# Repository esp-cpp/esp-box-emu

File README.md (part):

# esp-box-emu

<table style="padding:10px">
    <tr>
        <td></td>
        <td></td>
    </tr>
</table>

> A pocket-sized, Game Boy-style retro **emulation handheld** built around the
> ESP32-S3-BOX. Drop in a micro-SD card of ROMs and play NES, Game Boy / Color,
> Sega, MSX, and Genesis games — plus a full-speed port of **Doom** — on hardware
> you can 3D print and build yourself.

https://github.com/user-attachments/assets/2d3da6ea-2e80-42c3-bbd6-5a2c59601201

<!-- markdown-toc start - Don't edit this section. Run M-x markdown-toc-refresh-toc -->
**Table of Contents**

- [esp-box-emu](#esp-box-emu)
  - [Overview](#overview)
  - [Emulators](#emulators)
  - [Gallery](#gallery)
  - [Quick Start — Play It](#quick-start--play-it)
  - [Web Console](#web-console)
  - [Build the Hardware](#build-the-hardware)
  - [Build the Firmware](#build-the-firmware)
  - [ROMs and SD Card Setup](#roms-and-sd-card-setup)
    - [Boxart images](#boxart-images)
    - [metadata.csv format](#metadatacsv-format)
  - [Features and Roadmap](#features-and-roadmap)
  - [References and Inspiration](#references-and-inspiration)
  - [License](#license)

<!-- markdown-toc end -->

## Overview

The ESP-BOX-EMU turns an [ESP32-S3-BOX or
ESP32-S3-BOX-3](https://github.com/espressif/esp-box) into a handheld retro game
console. A custom add-on board and 3D-printed shell wrap the BOX in a Game Boy
Color form factor — real d-pad and buttons, battery, haptics, and a micro-SD
slot — and the firmware runs a stack of emulators behind a polished LVGL
interface with boxart, save states, and settings.

**Highlights**

- 🎮 **Six systems + Doom** — NES, Game Boy / Color, Sega Master System / Game
  Gear, Sega Genesis, and MSX 1/2 emulators, plus a full-speed **Doom** port —
  all with sound.
- 🧬 **Full-speed Genesis** — a custom **dual-core** port of gwenesis splits the
  emulation across both of the ESP32-S3's cores (CPU + video on one, the sound
  unit on the other) for full-speed Sega Genesis / Mega Drive *with* audio.
- ⚡ **No reboots** — every core and game loads on demand right from the menu, so
  you can jump between titles and even different systems without ever restarting
  the device.
- 🕹️ **Real controls** — d-pad, A/B/X/Y, Start/Select and volume buttons in a
  familiar Game Boy Color layout; the emulator is auto-selected from the ROM
  file extension.
- 💾 **Load from SD** — keep ROMs, boxart, and save states on a micro-SD card,
  and mount the card over USB-C as a mass-storage drive (TinyUSB MSC).
- 💤 **Save anywhere** — up to 5 save slots per game, each with an
  auto-generated screenshot shown in the load menu.
- 🔋 **Portable** — 1000 mAh LiPo battery with USB-C charging.
- 📳 **Haptics** — LRA haptic feedback (DRV2605), including in-game effects in
  Doom (weapon fire, taking damage, pickups, and more).
- 🖼️ **Polished UI** — LVGL menus for ROM select (with boxart) and settings
  (sound, brightness, display scaling, haptics), designed in Squareline Studio.
- 🌐 **Web console** — plug into a computer and Chrome or Edge offers a control
  panel: watch and play the screen, manage games and boxart, browse the SD
  card, change settings, and update the firmware, with nothing to install.
- 🛠️ **Fully open hardware** — 3D-printable GBC-style case and an open PCB
  (Fusion/Eagle **and** [atopile](https://atopile.io) + [KiCad](https://kicad.org)),
  all included in this repo.

## Emulators

The right emulator is chosen automatically from each ROM's file extension, and
games load on demand **straight from the menu — no reboot required**. Pick a
title, play, then drop back to the menu and launch a different game (or a
completely different system) without ever restarting the device. Every core runs
with audio, and several offer an **Unlocked mode** (toggle with the **X** button)
that removes the frame-rate cap for maximum speed.

| System | Core | Unlocked mode | Notes |
| --- | --- | :---: | --- |
| NES | [nofrendo](https://github.com/espressif/esp32-nesemu) | ✅ | D-Pad / A / B / Start / Select |
| Game Boy / Color | [gnuboy](https://github.com/rofl0r/gnuboy) | ✅ | D-Pad / A / B / Start / Select |
| Sega Master System / Game Gear | [smsplus](https://github.com/ekeeke/smsplus-gx) | ✅ | D-Pad / A / B / Start / Select |
| Sega Genesis / Mega Drive | [gwenesis](https://github.com/bzhxx/gwenesis) | — | Full speed with sound; 6-button pad (A→B, B→A, C→Y) |
| MSX 1 / 2 | [fmsx](https://fms.komkon.org/fMSX/) | — | D-Pad / A / B / Start / Select |
| Doom | [prboom](https://prboom.sourceforge.net/) | — | Full speed with audio **and haptic feedback** |
| Dark Forces | [The Force Engine](https://theforceengine.github.io/) (via [BSzili's Amiga port](https://github.com/BSzili/TheForceEngine/tree/amiga)) | — | Software renderer, iMuse sound effects and OPL3 music; see [Dark Forces setup](#dark-forces-setup) |
| PICO-8 | [femto8](https://github.com/benbaker76/femto8) | — | `.p8` and `.p8.png` carts; D-Pad, A/Y = O, B/X = X, START = PICO-8 pause menu; save states; cartdata saves to `pico8/cdata/`; see [PICO-8 setup](#pico-8-setup) |

Every core is a submodule ([esp-cpp/nofrendo](https://github.com/esp-cpp/nofrendo),
[gnuboy](https://github.com/esp-cpp/gnuboy), [smsplus](https://github.com/esp-cpp/smsplus),
[gwenesis](https://github.com/esp-cpp/gwenesis), [fmsx](https://github.com/esp-cpp/fmsx),
[prboom](https://github.com/esp-cpp/prboom), [TheForceEngine](https://github.com/esp-cpp/TheForceEngine),
[femto8](https://github.com/esp-cpp/femto8)): the core plus its `port/` glue to
`BoxEmu`, shared with [tab5-emu](https://github.com/esp-cpp/tab5-emu). Each
`components/<core>/CMakeLists.txt` here is the board's wrapper for it
(requirements, compile flags, linker fragment).

> 🧬 **Full-speed Genesis on the S3.** The Genesis core ships with a custom
> **dual-core** modification of gwenesis that spreads the workload across both of
> the ESP32-S3's CPU cores: **core 0** runs the 68000 CPU and VDP (video), while
> **core 1** runs the sound unit (Z80 + YM2612 FM synth + PSG). Sound-chip writes
> are queued and applied in order on core 1, which lets Genesis / Mega Drive
> games run at full speed *with* audio — something a single core can't keep up
> with.

<details>
<summary><strong>Doom controls and haptics</strong></summary>

**Controls:** **A** fire / enter · **B** strafe / backspace · **X** use ·
**Y** weapon toggle · **START** escape · **SELECT** map.

**Haptic feedback** is triggered when you fire a weapon (varies by weapon), take
damage (scaled to the health/armor lost), interact with something (e.g. a door),
or pick up a weapon, ammo, health, armor, a power-up, or a key / card.
</details>

<details>
<summary><strong>Dark Forces controls</strong></summary>

**In a mission:** **D-pad** move / turn · **A** fire · **B** jump · **X** use ·
**Y** next weapon · **START** escape menu. Hold **SELECT** as a modifier:
**SELECT + Left/Right** strafe · **SELECT + Down** crouch · **SELECT + Up**
automap · **SELECT + A** secondary fire · **SELECT + B** headlamp ·
**SELECT + X** gas mask · **SELECT + Y** previous weapon · **SELECT + START**
night vision. Running is always on.

**Menus, briefings and cutscenes:** the **D-pad** moves a virtual mouse cursor,
**A** clicks, **START** is Enter, **B** is Escape (skips cutscenes) and **Y** is
Space. Quitting from the game's escape menu returns to the emulator menu.

**Typing an agent name:** hold **SELECT**: **Right** adds a letter, **Up/Down**
change the last letter, **Left** deletes it; release SELECT and press **START**
to confirm.

The emulator's own pause menu (touch button or START+SELECT) still works for
video scaling and save slots; save slots only work while in a mission.
</details>

## Gallery

https://github.com/esp-cpp/esp-box-emu/assets/213467/3b77f6bd-4c42-417a-9eb7-a648f31b4008

https://github.com/esp-cpp/esp-box-emu/assets/213467/a3d18d03-c6a1-4911-89d1-e18119e8cc03

## Quick Start — Play It

Already have the add-on hardware (or an ESP32-S3-BOX you want to flash)? You
don't need to build anything from source — a prebuilt one-time **programmer** is
published with every release.

1. Download the `programmer` for your OS (`windows`, `macos`, or `linux`) from
   the latest [releases page](https://github.com/esp-cpp/esp-box-emu/releases).
2. Unzip it.
3. Run it: double-click the `.exe` on Windows, or run it from a terminal on
   macOS / Linux, e.g.:

   ```sh
   ./esp-box-emu_programmer_v1.0.0_macos.bin
   ```

   (The version in the filename matches the release you downloaded.)

Then [set up a micro-SD card](#roms-and-sd-card-setup) with your ROMs and you're
ready to play.

## Web Console

**Plug the emulator into a computer and it hands you a control panel.**
Connect the ESP-BOX-EMU's USB-C port to a computer running Chrome or Edge and
the browser pops up a notification pointing at
**[esp-cpp.github.io/esp-box-emu](https://esp-cpp.github.io/esp-box-emu/)**,
the firmware's WebUSB landing page. Click it, pick the emulator, and you're in:
no drivers, no app, no serial terminal. Watch the game being played,
take a screenshot, add a new game with its boxart, or update the firmware,
all from a browser tab.

What you can do from each tab:

- 📊 **Dashboard**: what's running right now (with its boxart), live frame-rate
  and memory graphs, the firmware and partition it booted from, why it last
  reset, and a button that hands the SD card to your PC as a USB drive.
- 🖥️ **Screen**: grab the game's (or the launcher's) screen, or turn on
  **Live** to keep it updating, and save it as a PNG. Play with the on-screen
  controller or your keyboard (arrows, Z / X / A / S, Enter = Start), save and
  load states in any slot, or quit the game.
- 📚 **Library**: every game on the card, grouped by console with its boxart
  and a game count per console. Search, filter by console (and, if you like,
  filter the handheld's launcher the same way), start any game with **Play**,
  or **Add a game**: drop in the ROM and a cover and the page uploads both and
  adds the line to `metadata.csv` for you. **Remove** takes one out again.
- 📁 **Files**: browse the SD card, download files, upload by drag and drop,
  create folders and delete things (handy for copying save states off the card).
- ⚙️ **Settings**: volume, mute, brightness, video scaling, resume last save
  and the haptic effect. The handheld's own menu shows each change right away,
  and it's saved to the card a moment later.
- 🔧 **System**: chip, flash, PSRAM, heap, ESP-IDF version, OTA state and the
  services on the link; restart the emulator (or into download mode for
  `idf.py flash`), and **Update firmware**, which restarts into the updater and
  opens the espp OTA console to send a new `build/esp-box-emu.bin`.
- 📜 **Console**: the device's log over Web Serial (pick the console's port),
  with a line filter, auto-follow, and save to a file.

**How it works:** the firmware's composite USB device includes a vendor
(WebUSB) interface that carries the same request/response link as
[`tools/emulink`](./tools/emulink), plus a USB descriptor that names the
landing page, which is how the browser knows where to send you. The page is
plain HTML, CSS and JavaScript modules in [`web/`](./web) (no build step),
published to GitHub Pages from `main`, and it talks to the device directly
from your browser; nothing goes through a server. Only one program can use the
link at a time, so close `emulink` (or the page) before switching between them.

Hacking on the page? Serve it locally with
`python3 -m http.server -d web 8000` and open http://localhost:8000 (WebUSB
needs https or localhost). See [`web/README.md`](./web/README.md) for the
details.

## Build the Hardware

The add-on is designed to match the Game Boy Color form factor and reuse GBC
button plastics and silicone membranes for an authentic feel. The shell is meant
to be 3D printed (PLA or PETG on a Prusa i3 mk3+) and assembled with M3 screws.

**Case / mechanical** — printable files are in [./mcad](./mcad) or on
[Printables](https://www.printables.com/model/396931-esp-box-emu). CAD is on
[Fusion 360 (free viewer)](https://a360.co/3le5oCQ):

**Electronics** — schematic and layout files are in [./ecad](./ecad), provided
as both Fusion/Eagle files and [atopile](https://atopile.io) +
[KiCad](https://kicad.org) sources. You can also order the board directly:

**GBC replacement buttons / membranes** used for a good play feel:

- [Silicone pads for Game Boy Color (1)](https://funnyplaying.com/collections/product/products/gbc-replacement-silicone-pads)
- [Silicone pads for Game Boy Color (2)](https://www.retromodding.com/products/game-boy-color-silicone-pads)
- [Game Boy Color button plastics](https://funnyplaying.com/collections/product/products/cgb-custom-buttons?variant=39333911920701)

## Build the Firmware

This repo uses submodules, so clone it recursively:

```sh
git clone --recurse-submodules git@github.com:esp-cpp/esp-box-emu
```

If you already cloned it non-recursively (or forgot the flag), pull the
submodules with:

```sh
git submodule update --init --recursive
```

Then build, flash, and open the serial monitor with [ESP-IDF](https://docs.espressif.com/projects/esp-idf/en/latest/esp32s3/get-started/index.html):

```sh
idf.py -C updater build   # once: the updater app, which goes in ota_1
idf.py -p PORT flash monitor
```

The updater (`updater/`) is what over-USB updates (`tools/emulink`) reboot
into, and what a bad update rolls back to, so build it before the first
flash: the emulator's `idf.py flash` then writes both. After that, updates
can go over USB with `emulink ota`.

Replace `PORT` with your board's serial port. To exit the monitor, type
`Ctrl-]`.

### Measuring performance and memory

The firmware prints greppable one-line reports on the serial console so a
captured play session doubles as a profile:

- `[mem] phase=boot|menu|launch|quit ...` — internal RAM / PSRAM free and
  largest free block at each phase, with `[mem] delta ...` lines at launch and
  quit relative to the menu (a non-zero delta after quitting is a leak or
  fragmentation).
- `[mem] block|region|task phase=...` — at boot and launch, every internal-RAM
  block above a threshold (labelled with the task whose stack it is), each
  registered heap region's used/free/largest, and every task's stack high-water
  mark (`stack_free_min`, repeated at quit after a full play session).
- `[genesis mem] NAME: N bytes -> INTERNAL|PSRAM` — where each big emulator
  buffer landed (the Genesis gets noticeably slower when its hot buffers fall
  back to PSRAM).
- `[genesis perf] fps=.. frame=..us 68k=..us vdp=..us convert=..us barrier=..us ...` —
  per-frame time breakdown averaged over the last 300 frames (~5 s): 68000,
  VDP render, RGB565 conversion, time core 0 spends waiting for the core-1
  sound unit, present/audio, pacing sleep, `late=`/`skipped=`/`dropped=`
  frame counts (skipped = emulated without rendering because the panel could
  not show the frame), `blit=` (video task time per displayed frame), the
  core-1 sound unit's own frame time, and Z80 counters (`irq=` V-ints taken,
  `busreq=`, `halted=` scanline slices lost to a held bus, `wto=` handshake
  timeouts, `ymw=` Z80→YM2612 writes). Compile with `GENESIS_PERF=0` to
  remove it.
- `[display] lcd spi clock: N Hz` — the clock the LCD SPI device actually got
  (the ESP32-S3 can only divide 80 MHz by integers, so a 60 MHz request runs
  at 40 MHz: 320×240×16bpp is ~31 ms per frame, the panel's ~31 fps ceiling).

Capture and summarise a session (performance PRs should include a before/after
from the same game and the same ~1 minute of play):

```sh
python tools/serial_capture.py PORT --out before.log --until "delta phase=quit"
# ... flash the change, play the same section again ...
python tools/serial_capture.py PORT --out after.log --until "delta phase=quit"
python tools/perf_report.py before.log after.log
```

`perf_report.py` prints each run's launch/quit memory, buffer placement, and
the perf-line averages side by side with deltas.

## ROMs and SD Card Setup

Format a micro-SD card as **FAT** and add your ROMs (`.nes`, `.gb`, `.gbc`, …),
boxart images (`.jpg`), and a `metadata.csv` file (see the example
[metadata.csv](./metadata.csv)).

### Boxart images

Boxart displays best at 100 px wide. The
[./boxart/source/resize.bash](./boxart/source/resize.bash) script resizes every
`.jpg` in `boxart/source` to 100 px wide (preserving aspect ratio) and writes the
results to the `boxart` folder. Copy those onto the SD card and reference them
from your metadata file.

### Dark Forces setup

Dark Forces is played with the original (purchased) game data; the engine does
not include it. Copy the DOS install files onto the SD card into a single
folder, for example `darkforces/`:

```
darkforces/DARK.GOB
darkforces/SOUNDS.GOB
darkforces/SPRITES.GOB
darkforces/TEXTURES.GOB
darkforces/LFD/*.LFD       (menus, briefings and cutscenes)
```

Then reference `DARK.GOB` from `metadata.csv`:

```csv
darkforces/DARK.GOB, boxart/darkforces.jpg, Star Wars: Dark Forces
```

Settings (`settings.ini`) and agent / save files are written to the same folder.

### PICO-8 setup

PICO-8 carts are plain `.p8` text files or `.p8.png` cartridge images. Put them
in a folder on the card (for example `pico8/`) and reference them from
`metadata.csv`:

```csv
pico8/celeste.p8, boxart/celeste.jpg, Celeste Classic
```

Carts that use `cartdata()` save to `pico8/cdata/`. The 128x128 screen shows
1:1 in the "original" video mode and scaled to 240x240 in "fit". Multi-cart
games that `load("#id")` their other carts work when those carts sit in the
same folder as `id.p8.png` / `id.p8`.

What to expect: the Lua interpreter runs at roughly 1.3M instructions per
second on the S3 (its heap lives in PSRAM), enough for carts of Celeste's
weight at full speed, but CPU-heavy carts close to PICO-8's limit run at a
few frames per second. Save states work (the cart's Lua heap and PICO-8
RAM are snapshotted between frames); carts' own `cartdata()` saves are kept
separately; there is no mouse or keyboard.

### metadata.csv format

Each line maps a ROM to its boxart and display name:

```csv
<rom filename>, <rom boxart filename>, <rom display name>
```

Example:

```csv
mario.nes, boxart/mario.jpg, Mario Bros.
super_mario_1.nes, boxart/super_mario_bros_1.jpg, Super Mario Bros.
super_mario_3.nes, boxart/super_mario_bros_3.jpg, Super Mario Bros. 3
zelda.nes, boxart/zelda1.jpg, The Legend of Zelda
zelda_2.nes, boxart/zelda2.jpg, The Legend of Zelda 2: the Adventure of Link
mega_man.nes, boxart/megaman1.jpg, MegaMan
metroid.nes, boxart/metroid1.jpg, Metroid
pokemon_blue.gb, boxart/pokemon_blue.jpg, Pokemon Blue
pokemon_red.gb, boxart/pokemon_red.jpg, Pokemon Red
pokemon_yellow.gbc, boxart/pokemon_yellow.jpg, Pokemon Yellow
links_awakening.gb, boxart/tloz_links_awakening.jpg, The Legend of Zelda: Link's Awakening
links_awakening.gbc, boxart/tloz_links_awakening_dx.jpg, The Legend of Zelda: Link's Awakening DX
```

## Features and Roadmap

A checklist of what's implemented and what's still in progress.

**Emulation**

- [x] Auto-select emulator by ROM extension: NES, GB/GBC, SMS/GG, MSX, Genesis, Doom, Dark Forces, PICO-8
- [x] On-demand core loading — every emulator and game loads at runtime with no reboot needed to switch games or systems
- [x] Custom **dual-core Genesis** (gwenesis): 68000 + VDP on one ESP32-S3 core, sound unit (Z80 + YM2612 + PSG) on the other, for full-speed audio and gameplay
- [x] Doom haptic feedback :rocket:
- [x] Save state (with automatic save-screenshot creation to the SD card)
- [x] Load state — up to 5 slots per game, with save-screenshot previews
- [x] Shared-memory system so many emulators can be built in together while keeping their hot state in fast internal RAM
- [x] Dark Forces (The Force Engine port; software renderer with sound and music)
- [ ] SNES emulator (WIP)

**User interface**

- [x] LVGL ROM-select menu with boxart and title, navigable by controller
- [x] Games grouped by console: left / right jump to the previous / next
  console, and the console in the header (tap it, or press X) opens a picker
  that shows only one console's games (outlined while filtered; `emulink
  filter <console>` over USB)
- [x] LVGL settings menu (volume, video, haptics) and in-game pause menu
- [x] GUI data (titles + boxart) loaded from the [metadata file](./metadata.csv)
- [x] Squareline Studio source for the LVGL boilerplate ([SLS files](./squareline), [generated files](./components/gui/generated))

**Video and audio**

- [x] Emulator framebuffers in SPIRAM, with queued screen transfers for maximum draw speed
- [x] Video scaling with ORIGINAL, FIT, and FILL display modes
- [x] Audio output over I2S via the es8311 codec ([codec component](./components/codec))
- [x] Mute button toggles audio while a ROM is running
- [x] Haptic feedback via a DRV2605-driven LRA
- [ ] Decorative graphics in the black borders during NES / GB/C emulation (WIP)

**Storage and input**

- [x] micro-SD (FAT) filesystem over SPI
- [x] TinyUSB MSC device to expose the SD card to an attached USB host
- [x] Memory-mapping of the selected ROM from storage into a raw data partition (SPI flash)
- [x] D-pad + A/B/X/Y + Start/Select input (MCP23x17 on v0 hardware, AW9523 on v1)
- [x] Touchscreen input ([tt21100 component](./components/tt21100))

**Hardware**

- [x] Control-board schematic / layout: joystick / d-pad / buttons (via I²C I/O expander + ADC), battery, charger, DRV2605 haptics, micro-SD, boost converter, and USB 2.0 passthrough from USB-C
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
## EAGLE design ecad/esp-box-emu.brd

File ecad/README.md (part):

# ESP-BOX-EMU ecad

This folder contains the electronic design of the ESP-BOX-EMU.

The ESP-BOX-EMU contains a single circuit board with the following components:
- USB-C connector
- Conductive / Membrane switches for d-pad, abxy, and start/select buttons which mate with GBC membranes and buttons
- Tactile switches for Volume +/-
- RED LED for charging indication
- DRV2605L haptic driver
- JST-PH connector for the LiPo battery
- AW9523 I/O expander
- MCP73831 LiPo charger
- MAX17048 LiPo state-of-charge monitor (I2C)
- MicroSD card slot
- TPS63020 5V buck-boost converter (battery -> 5V for the box)

These features are supported in two different versions of the electronics, targeting:
- ESP32-S3-Box
- ESP32-S3-Box-3

## Layout of this folder

- `elec/src/` - atopile sources (modern atopile >= 0.15 syntax)
- `elec/src/parts/` - atomic parts (auto-generated from LCSC plus local
  custom parts for the GBC membranes/buttons, board outlines and edge fingers)
- `elec/layout/` - KiCad layouts, one folder per build (netlist-synced by
  `ato build`; placement/routing edits are preserved)
- `scripts/` - layout automation (MCAD position export, scripted placement,
  base/connector layout sync)
- `Box Electronics v*.sch/brd`, `Box-3 Electronics v*.sch/brd` - the
  Fusion 360 / Eagle design the boards were actually manufactured from

The pre-migration atopile 0.2 sources, the old shared footprint library and
the old routed KiCad-6 boards were removed after the 0.15 migration; they
are available in git history (pre-2026-07) if ever needed.

## Setup

``` sh
# one time steps on your machine (any of these; uv shown)
uv tool install --python 3.14 atopile
```

Dependencies (e.g. `atopile/ti-tps63020`) are fetched automatically into
`.ato/modules/` on first build; `ato add <package>` adds new ones.

## Build

``` sh
# build everything
ato build

# build for ESP32-S3-BOX
ato build -b box-emu

# build for ESP32-S3-BOX-3
ato build -b box-3-emu
```

### Offline build (atopile 0.16 service migration)

As part of atopile's 0.16 platform migration (services moving from
`*.atopileapi.com` / `packages.atopile.io` to `app.atopile.io`), the hosted
components-picker API used by the 0.15.x CLI
(`components.atopileapi.com`) was taken offline, and no public replacement
endpoint exists for the CLI yet. Until atopile publishes a CLI that speaks
to the new services, build via the local stand-in server, which answers
picker queries from the part data already pinned in this repo:

``` sh
scripts/ato-build-offline.sh                 # all targets
scripts/ato-build-offline.sh -b box-emu-base # one target
```

Two caveats:

- Footprints/symbols still come from `build/cache/parts/easyeda/` (or the
  still-alive EasyEDA API). If the cache is stale (>1 day old), refresh the
  `atopile_queried_at` stamps inside the cached `C*.json` files rather than
  hammering EasyEDA's rate limiter with re-downloads.
- The stand-in returns no part *attributes*, so builds rewrite the hidden
  parameter annotations in the layouts to the design constraints (e.g. a
  resistor annotated `10kΩ ±1%` from the real part data becomes `±5%` from
  the design). The picked LCSC parts, BOM and copper are unchanged; a
  normal online build will restore the exact annotations once the service
  returns.

## Continuous integration

`.github/workflows/atopile.yml` (official `atopile/setup-atopile@v2` action)
builds every target from the checked-in sources with
`ato build --keep-picked-parts --keep-net-names --keep-designators`, then
runs `scripts/canonicalize-boards.py --all` and fails if `git diff` shows
any change to `elec/layout` or `elec/src` -- i.e. the checked-in design
must be exactly reproducible. (We don't use `ato build --frozen`: atopile
0.15.x writes KiCad group member lists in nondeterministic order, which
makes frozen flaky; the canonicalize+diff check gives the same guarantee
robustly.) It then exports gerbers, pick & place, BOM, STEP, GLB and a
rendered PNG for `box-emu` and `box-3-emu` (`-t all -t 3d-image`), plus
top/bottom PDFs via the kicad-cli bundled in the atopile container.
Artifacts are uploaded per board and attached to releases as zips.

Two reproducibility rules this relies on:

- **Parts are pinned.** None of the part `.ato` files carry the
  `is_auto_generated` trait: atopile would otherwise re-download every
  picked part from the EasyEDA API on each build and *replace* the
  checked-in part directory whenever the API response differs (which it
  does between regions, over time, and during their frequent partial
  outages). Without the trait, atopile logs "not overwriting" and the
  repo stays the source of truth. To intentionally update a part, delete
  its directory and re-run `ato create part --search <LCSC>`.
- **After local layout sessions**, run `ato build` +
  `python3 scripts/canonicalize-boards.py --all` and commit the result,
  so CI's rebuild matches byte-for-byte.

The LCSC/EasyEDA API has multi-hour outages; build steps retry, but a
run during a hard outage will still fail at part picking -- just re-run
it later.

## Ordering / manufacturing notes

**Surface finish: order ENIG, not HASL.** The GBC button footprints expose
bare-copper interdigitated fingers that the carbon membrane pucks press
against. With HASL those fingers come back coated in solder (uneven, prone
to oxidation) and the buttons work poorly; with ENIG they come back flat
gold, which is the standard finish for carbon-contact keypads. This is a
per-order fab option (JLCPCB: "Surface Finish" -> "ENIG") and cannot be
enforced from the design files.

Related, already handled in the footprints: the buttons' four corner
connection pads are tented (copper-only, no paste, no mask opening), so
PCBA assembly applies no solder anywhere on the button contact areas. If
you regenerate or edit `GBC_*_BUTTON` footprints, keep the pads
`(layers "F.Cu")` only.

## Working on the KiCad layouts

Each build owns one board file: `elec/layout/<build>/<build>.kicad_pcb`
(KiCad 9+ format; there is no `.kicad_pro` — open the `.kicad_pcb` directly
in KiCad's PCB Editor). The `fp-lib-table` next to each board resolves all
footprints from the atomic parts in `elec/src/parts/`, so the boards are
self-contained as long as the repo layout is intact.

The `.ato` sources are the source of truth for everything electrical;
KiCad is only for placement and routing:

``` sh
# build a target and open its layout in KiCad in one step
ato build -b box-3-emu --open

# or open it manually
open "elec/layout/box-3-emu/box-3-emu.kicad_pcb"
```

The edit loop:

1. Change schematics by editing the `.ato` files (never add/remove
   components or change connectivity in KiCad — the next build will
   revert it).
2. Run `ato build -b <build>`. This syncs footprints and nets into the
   board file. Footprints are matched by their `atopile_address` property,
   so your existing placement and routing are preserved; new components
   appear stacked near the origin for you to place.
3. Place/route in KiCad and save. **Close the board (or at least save it)
   before the next `ato build`** — atopile rewrites the file on disk, and
   KiCad's PCB editor will not auto-reload; reopen the file after each
   build. A stale `~<name>.kicad_pcb.lck` file means KiCad still has it
   open.

Useful flags when iterating on layout: `--keep-designators`,
`--keep-net-names`, and `--keep-picked-parts` take those from the existing
PCB instead of regenerating them, and `--frozen` fails the build if the
PCB would change at all (good for CI).

Recovering from common accidents:

- **Deleted a footprint in KiCad?** Harmless to the design -- the `.ato`
  source is the source of truth, and the next `ato build -b <build>`
  re-adds it (near the origin; its placement is lost, its part gets
  re-picked). Restore known positions with `place-parts.py apply` if it
  was a mechanically-placed part. It's worth running
  `place-parts.py dump` into `positions.json` after every good layout
  session (and committing it) so *every* part's placement has a snapshot.
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
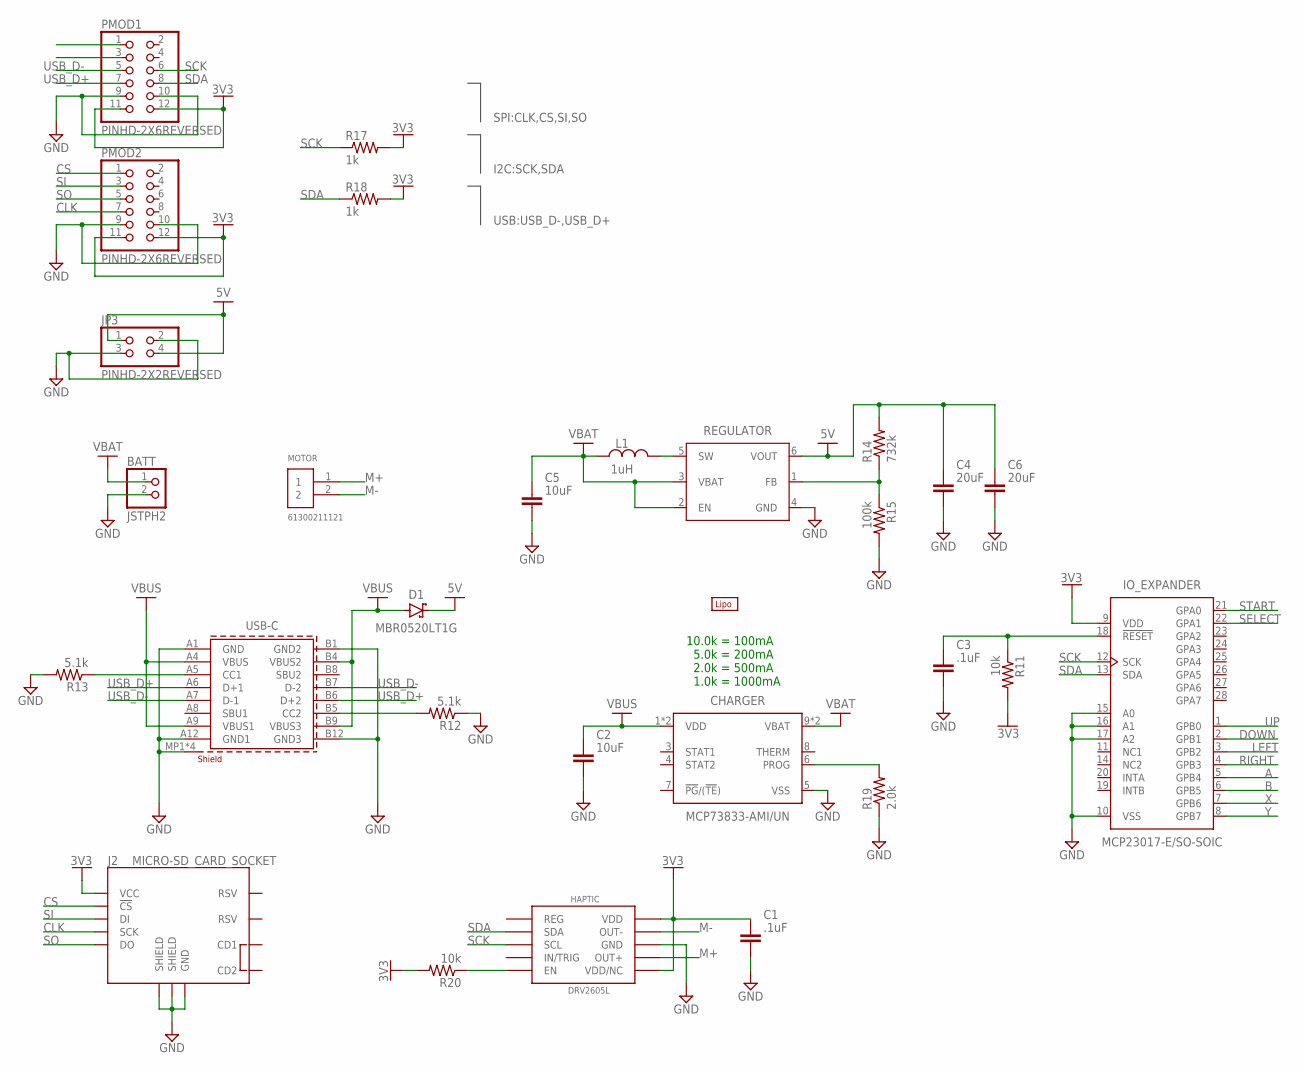
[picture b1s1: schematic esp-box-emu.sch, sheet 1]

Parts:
BATT: JSTPH2
BT1: LIPO-OUTLINE1100; LIPO-1000
C1, C3: .1uF; CAPC1608X85
C2, C5: 10uF; CAPC1608X85
C4, C6: 20uF; CAPC2012X110
CHARGER: MCP73833-AMI/UN; SOP50P490X110-10
D1: MBR0520LT1G; SODFL3718X115
HAPTIC: DRV2605L; VSSOP-10
IO_EXPANDER: MCP23017-E/SO-SOIC; SOIC127P1030X265-28
J2: MICRO-SD_CARD_SOCKET; MICRO-SD-SOCKET
JP3: PINHD-2X2REVERSED; 2X02/EDGE_REVERSED
L1: 1uH; INDM3225X240
MOTOR: 61300211121
PMOD1, PMOD2: PINHD-2X6REVERSED; 2X06/EDGE_REVERSED
R11, R20: 10k; RESC1608X60
R12, R13: 5.1k; RESC1608X60
R14: 732k; RESC1608X60
R15: 100k; RESC1608X60
R17, R18: 1k; RESC1608X60
R19: 2.0k; RESC1608X60
REGULATOR: TPS61070; SOT563
USB-C: 629722000214; USB4110GFA

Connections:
3V3: C1.1, HAPTIC.P$6 (VDD/NC), HAPTIC.P$10 (VDD), IO_EXPANDER.9 (VDD), J2.VCC, PMOD1.11, PMOD1.12, PMOD2.11, PMOD2.12, R11.2, R17.2, R18.2, R20.2; also elsewhere on the board
5V: C4.1, C6.1, D1.1 (C), JP3.1, JP3.4, R14.2, REGULATOR.6 (VOUT)
A: IO_EXPANDER.5 (GPB4); also elsewhere on the board
B: IO_EXPANDER.6 (GPB5); also elsewhere on the board
CLK: J2.SCLK (SCK), PMOD2.7
CS: J2.CS (!CS), PMOD2.1
DOWN: IO_EXPANDER.2 (GPB1); also elsewhere on the board
GND: BATT.2, C1.2, C2.2, C3.2, C4.2, C5.2, C6.2, CHARGER.5 (VSS), HAPTIC.P$8 (GND), IO_EXPANDER.10 (VSS), IO_EXPANDER.15 (A0), IO_EXPANDER.16 (A1), IO_EXPANDER.17 (A2), J2.GND, J2.GND1 (SHIELD), J2.GND3 (SHIELD), JP3.2, JP3.3, PMOD1.9, PMOD1.10, PMOD2.9, PMOD2.10, R12.1, R13.2, R15.2, R19.1, REGULATOR.4 (GND), USB-C.A1 (GND), USB-C.A12 (GND1), USB-C.B1 (GND2), USB-C.B12 (GND3), USB-C.MP1 (SHIELD), USB-C.MP2 (SHIELD), USB-C.MP3 (SHIELD), USB-C.MP4 (SHIELD); also elsewhere on the board
LEFT: IO_EXPANDER.3 (GPB2); also elsewhere on the board
M+: HAPTIC.P$7 (OUT+), MOTOR.1
M-: HAPTIC.P$9 (OUT-), MOTOR.2
unnamed: C3.1, IO_EXPANDER.18 (!RESET), R11.1
unnamed: R12.2, USB-C.B5 (CC2)
unnamed: R13.1, USB-C.A5 (CC1)
unnamed: R14.1, R15.1, REGULATOR.1 (FB)
unnamed: L1.2, REGULATOR.5 (SW)
unnamed: CHARGER.6 (PROG), R19.2
unnamed: HAPTIC.P$5 (EN), R20.1
RIGHT: IO_EXPANDER.4 (GPB3); also elsewhere on the board
SCK: HAPTIC.P$2 (SCL), IO_EXPANDER.12 (SCK), PMOD1.6, R17.1
SDA: HAPTIC.P$3 (SDA), IO_EXPANDER.13 (SDA), PMOD1.8, R18.1
SELECT: IO_EXPANDER.22 (GPA1); also elsewhere on the board
SI: J2.DI, PMOD2.3
SO: J2.DO, PMOD2.5
START: IO_EXPANDER.21 (GPA0); also elsewhere on the board
UP: IO_EXPANDER.1 (GPB0); also elsewhere on the board
USB_D+: PMOD1.7, USB-C.A6 (D+1), USB-C.B6 (D+2)
USB_D-: PMOD1.5, USB-C.A7 (D-1), USB-C.B7 (D-2)
VBAT: BATT.1, C5.1, CHARGER.9 (VBAT), CHARGER.10 (VBAT), L1.1, REGULATOR.2 (EN), REGULATOR.3 (VBAT)
VBUS: C2.1, CHARGER.1 (VDD), CHARGER.2 (VDD), D1.2 (A), USB-C.A4 (VBUS), USB-C.A9 (VBUS1), USB-C.B4 (VBUS2), USB-C.B9 (VBUS3)
X: IO_EXPANDER.7 (GPB6); also elsewhere on the board
Y: IO_EXPANDER.8 (GPB7); also elsewhere on the board

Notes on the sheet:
10.0k = 100mA 5.0k = 200mA 2.0k = 500mA 1.0k = 1000mA

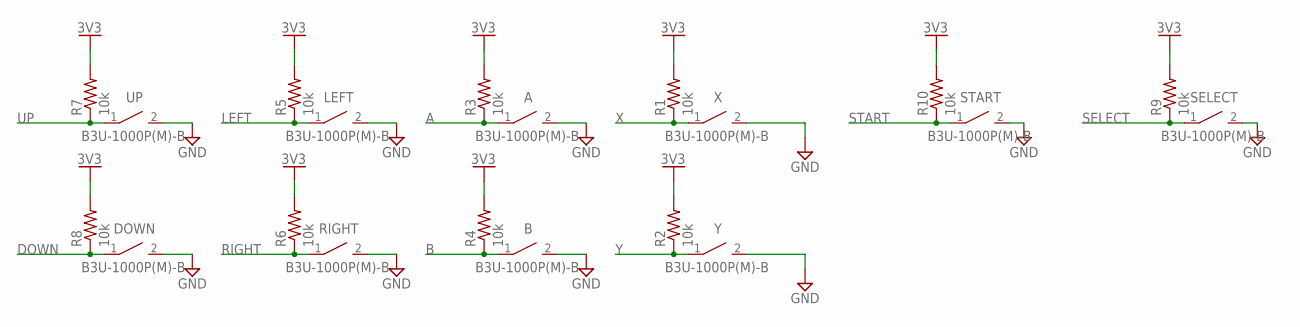
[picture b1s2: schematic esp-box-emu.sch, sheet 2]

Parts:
A: B3U-1000P(M)-B
B: B3U-1000P(M)-B
DOWN: B3U-1000P(M)-B
LEFT: B3U-1000P(M)-B
R1, R2, R3, R4, R5, R6, R7, R8, R9, R10: 10k; RESC1608X60
RIGHT: B3U-1000P(M)-B
SELECT: B3U-1000P(M)-B
START: B3U-1000P(M)-B
UP: B3U-1000P(M)-B
X: B3U-1000P(M)-B
Y: B3U-1000P(M)-B

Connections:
3V3: R1.2, R2.2, R3.2, R4.2, R5.2, R6.2, R7.2, R8.2, R9.2, R10.2; also elsewhere on the board
A: A.1, R3.1; also elsewhere on the board
B: B.1, R4.1; also elsewhere on the board
DOWN: DOWN.1, R8.1; also elsewhere on the board
GND: A.2, B.2, DOWN.2, LEFT.2, RIGHT.2, SELECT.2, START.2, UP.2, X.2, Y.2; also elsewhere on the board
LEFT: LEFT.1, R5.1; also elsewhere on the board
RIGHT: R6.1, RIGHT.1; also elsewhere on the board
SELECT: R9.1, SELECT.1; also elsewhere on the board
START: R10.1, START.1; also elsewhere on the board
UP: R7.1, UP.1; also elsewhere on the board
X: R1.1, X.1; also elsewhere on the board
Y: R2.1, Y.1; also elsewhere on the board

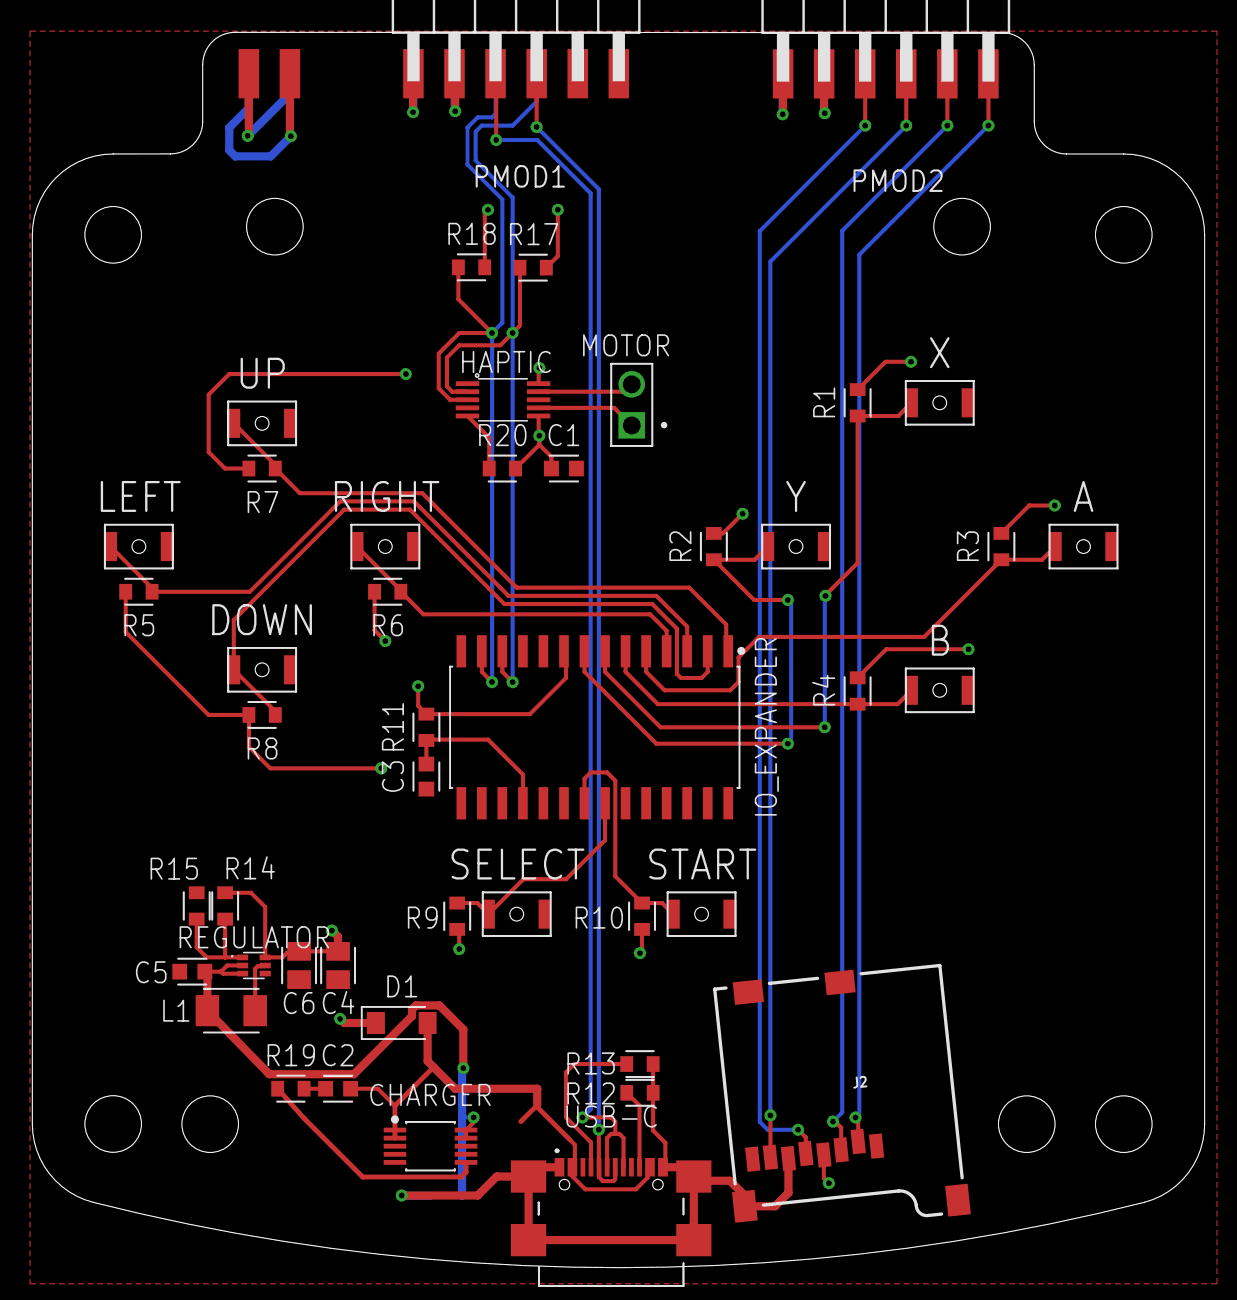
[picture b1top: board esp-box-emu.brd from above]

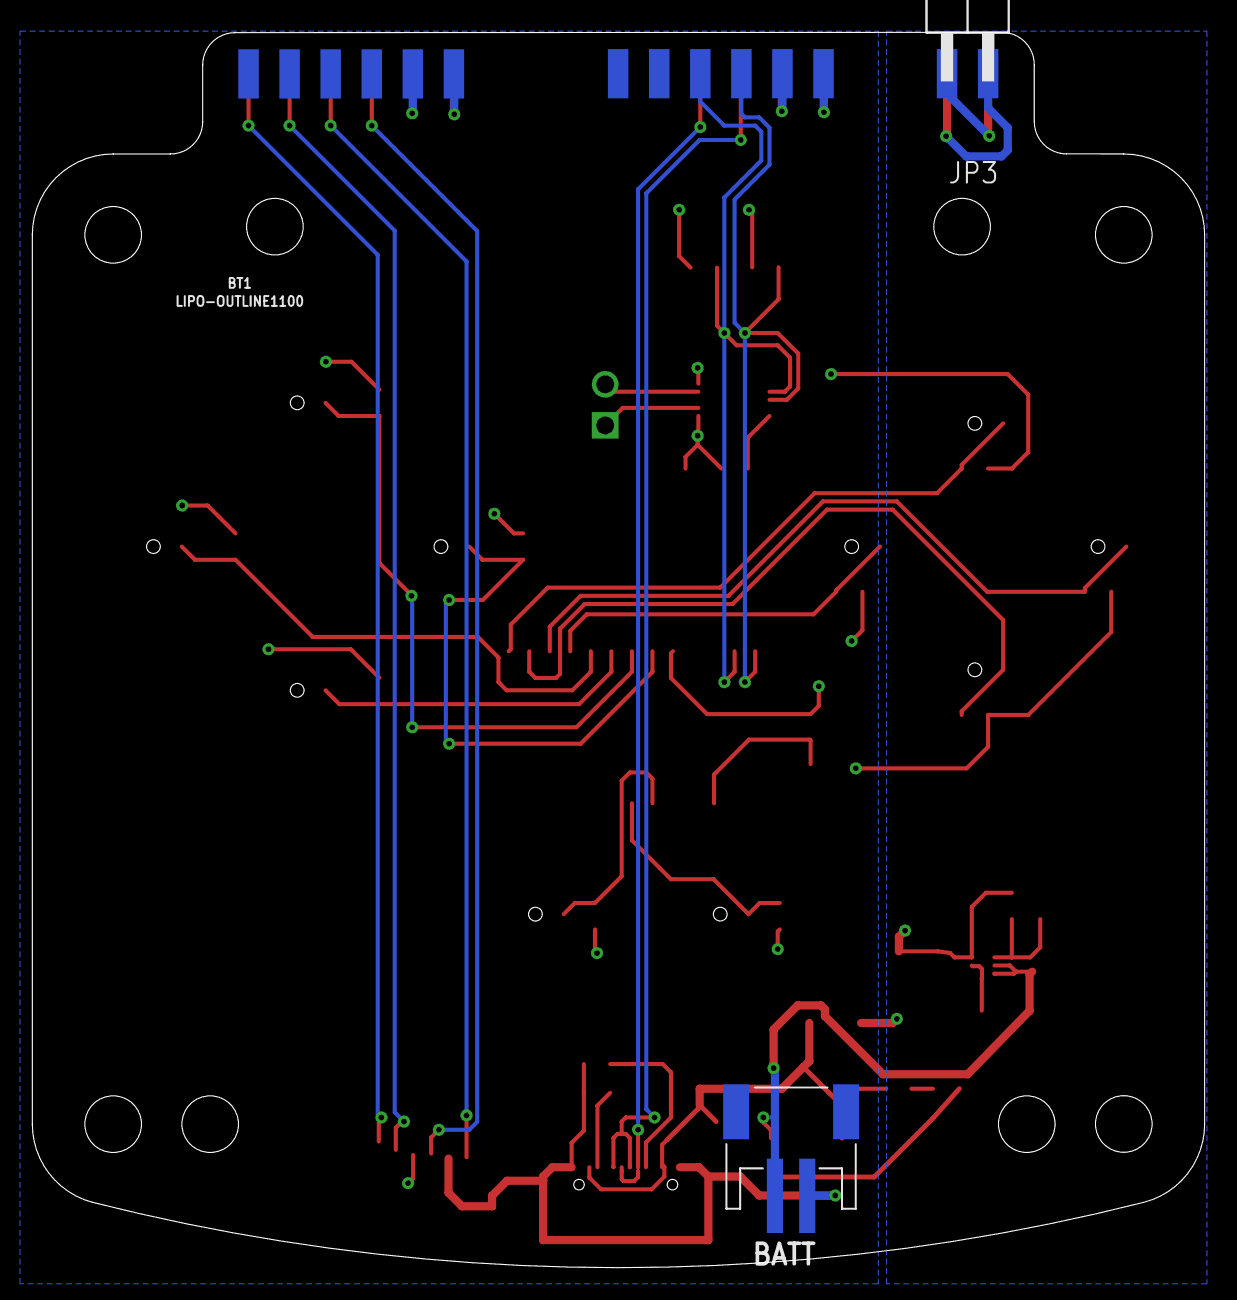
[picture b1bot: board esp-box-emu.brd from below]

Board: 2 copper layers, 72.5 x 76.4 mm, 49 parts (3 on the bottom side), 32 nets.

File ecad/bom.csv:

"Qty";"Value";"Device";"Package";"Parts";"Description";"";
"2";".1uF";"C_CHIP-0603(1608-METRIC)";"CAPC1608X85";"C1, C3";"Capacitor - Generic";"";
"1";"100k";"R-US_CHIP-0603(1608-METRIC)";"RESC1608X60";"R15";"Resistor Fixed - ANSI";"";
"12";"10k";"R-US_CHIP-0603(1608-METRIC)";"RESC1608X60";"R1, R2, R3, R4, R5, R6, R7, R8, R9, R10, R11, R20";"Resistor Fixed - ANSI";"";
"2";"10uF";"C_CHIP-0603(1608-METRIC)";"CAPC1608X85";"C2, C5";"Capacitor - Generic";"";
"2";"1k";"R-US_CHIP-0603(1608-METRIC)";"RESC1608X60";"R17, R18";"Resistor Fixed - ANSI";"";
"1";"1uH";"L_MOLDED-1210(3225-METRIC)";"INDM3225X240";"L1";"Inductor Fixed - Generic";"";
"1";"2.0k";"R-US_CHIP-0603(1608-METRIC)";"RESC1608X60";"R19";"Resistor Fixed - ANSI";"";
"2";"20uF";"C_CHIP-0805(2012-METRIC)";"CAPC2012X110";"C4, C6";"Capacitor - Generic";"";
"2";"5.1k";"R-US_CHIP-0603(1608-METRIC)";"RESC1608X60";"R12, R13";"Resistor Fixed - ANSI";"";
"1";"61300211121";"61300211121";"61300211121";"MOTOR";"CONN HEADER VERT 2POS 2.54MM";"";
"1";"629722000214";"629722000214SMD";"USB4110GFA";"USB-C";"WR-COM USB 2.0 Type C Plug Vertical SMT";"";
"1";"732k";"R-US_CHIP-0603(1608-METRIC)";"RESC1608X60";"R14";"Resistor Fixed - ANSI";"";
"10";"B3U-1000P(M)-B";"B3U-X000B3U-1000P(M)-B1000P(M)-B";"B3U-1000P(M)-B";"A, B, DOWN, LEFT, RIGHT, SELECT, START, UP, X, Y";"Ultra-small Tactile Switch";"";
"1";"DRV2605L";"DRV2605L";"VSSOP-10";"HAPTIC";"";"";
"1";"JSTPH2";"JSTPH2";"JSTPH2";"BATT";"";"";
"1";"LIPO-OUTLINE1100";"LIPO-OUTLINE1100";"LIPO-1000";"BT1";"LiPo Battery Outlines";"";
"1";"MBR0520LT1G";"SCHOTTKY_MBR0520LT1GDO-219";"SODFL3718X115";"D1";"Schottky Diode - Popular parts";"";
"1";"MCP23017-E/SO-SOIC";"MCP23017-E/SO-SOIC";"SOIC127P1030X265-28";"IO_EXPANDER";"16-Bit I/O Expander with Serial Interface";"";
"1";"MCP73833-AMI/UN";"MCP73833-AMI/UN";"SOP50P490X110-10";"CHARGER";"Li-Ion / Li-Polymer Charge Management Controller";"";
"1";"MICRO-SD_CARD_SOCKET";"MICRO-SD_CARD_SOCKET";"MICRO-SD-SOCKET";"J2";"microSD Socket for Transflash";"";
"1";"PINHD-2X2REVERSED";"PINHD-2X2REVERSED";"2X02/EDGE_REVERSED";"JP3";"PIN HEADER";"";
"2";"PINHD-2X6REVERSED";"PINHD-2X6REVERSED";"2X06/EDGE_REVERSED";"PMOD1, PMOD2";"PIN HEADER";"";
"1";"TPS61070";"TPS61023";"SOT563";"REGULATOR";"Synchronous Boost Converter With 600-mA Switch";"";

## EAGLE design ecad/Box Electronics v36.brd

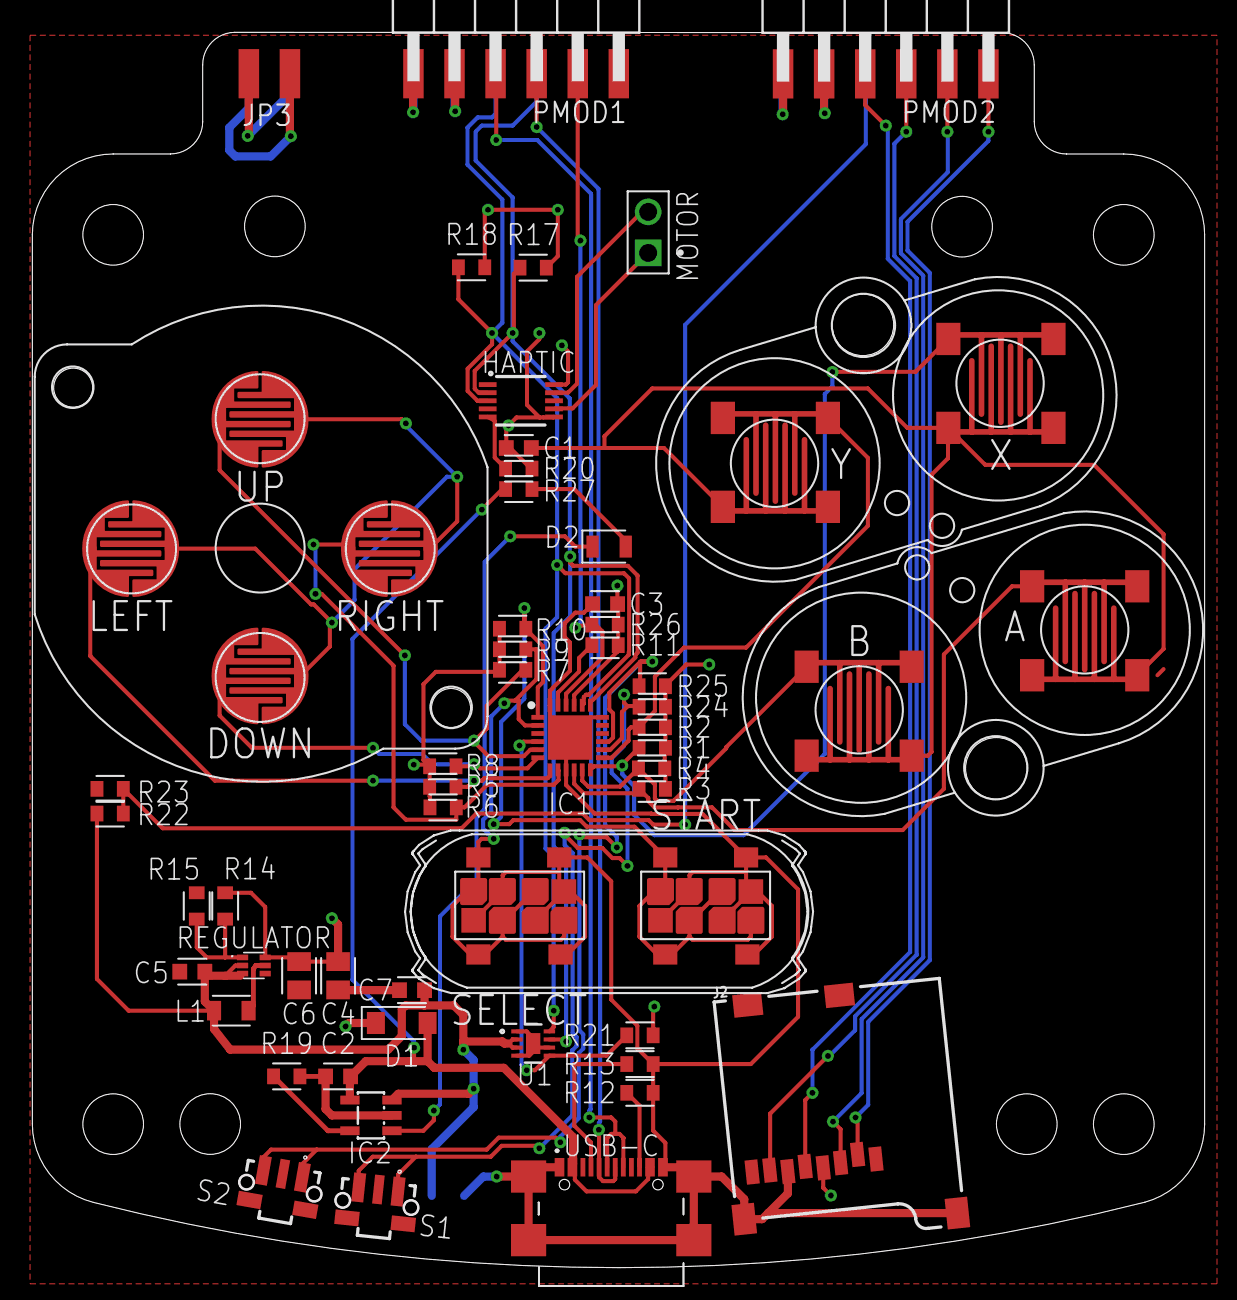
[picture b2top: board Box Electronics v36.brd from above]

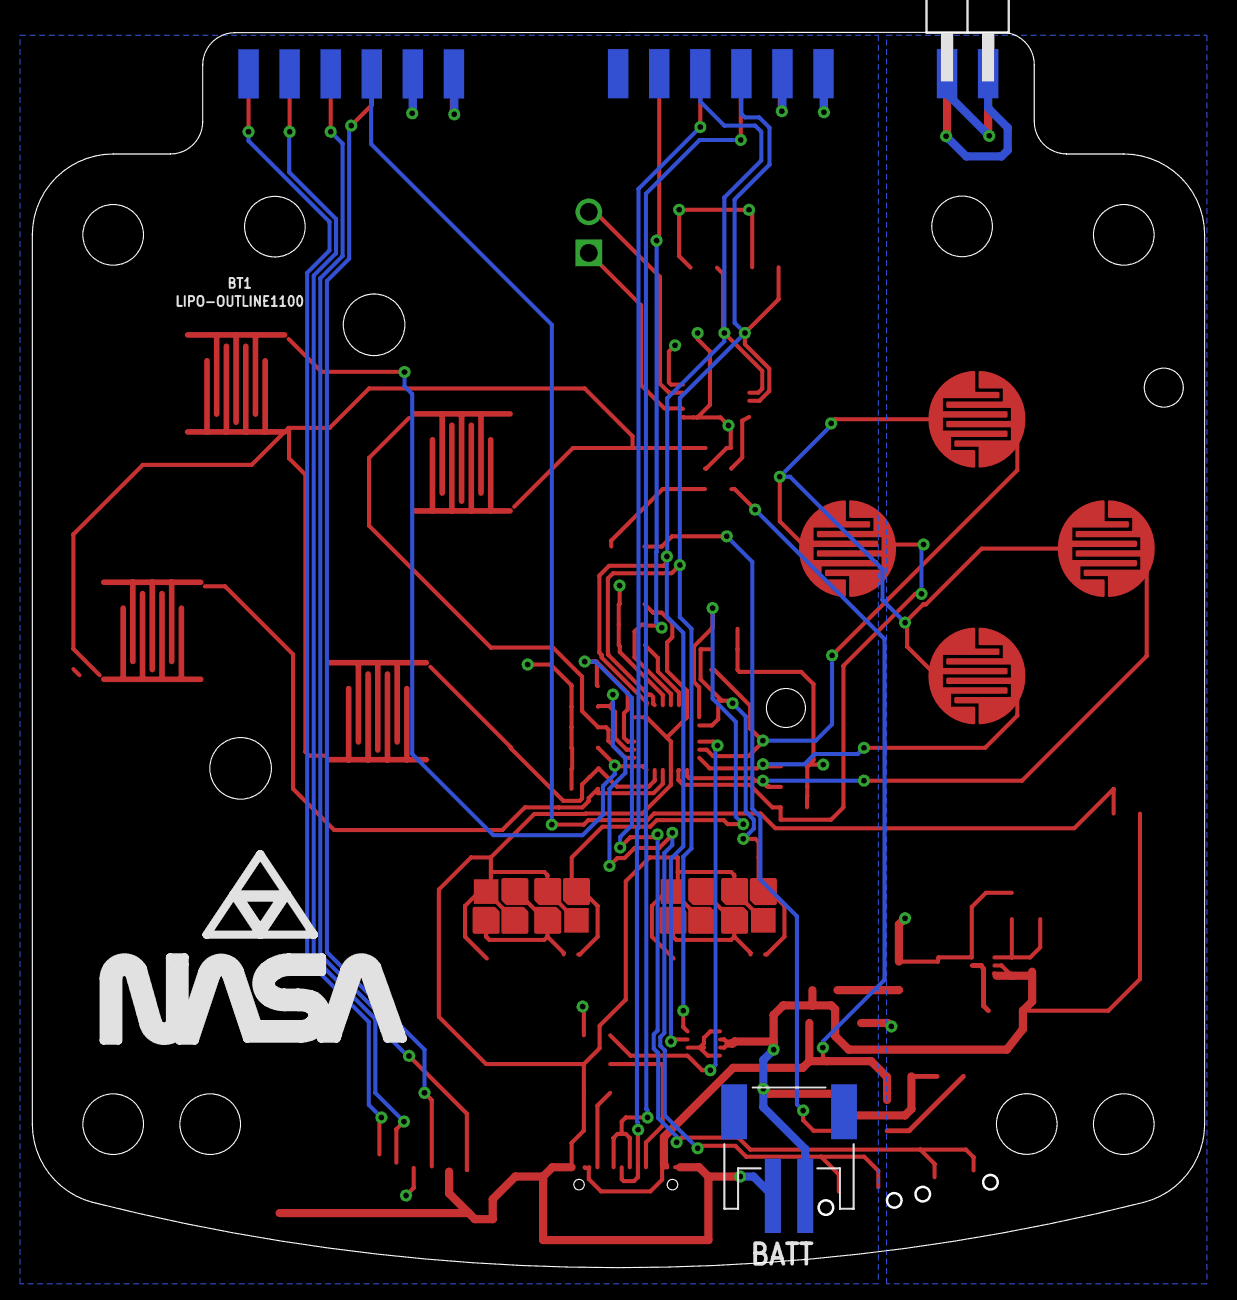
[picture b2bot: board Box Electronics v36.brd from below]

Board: 2 copper layers, 72.5 x 76.4 mm, 65 parts (3 on the bottom side), 39 nets.

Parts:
A: SWITCH_MOMENTARYDMG-BTN-A/B; DMG_BTN3
B: SWITCH_MOMENTARYDMG-BTN-A/B; DMG_BTN3
BATT: JSTPH2
BT1: LIPO-OUTLINE1100; LIPO-1000
C1, C3, C7: .1uF; CAPC1608X85
C2, C5: 10uF; CAPC1608X85
C4, C6: 22uF; CAPC2012X110
D1: MBR0520LT1G; SODFL3718X115
D2: LED_RED; LEDC2012X110N_FLAT-R
DOWN: SWITCH_MOMENTARYCONTACTIVE_6MM_2; BUTTON-CONDUCTIVE_6MM_2
HAPTIC: DRV2605L; VSSOP-10
IC1: AW9523BTQR; QFN50P400X400X80-25N
IC2: MCP73831/OT; SOT23-5L
J2: MICRO-SD_CARD_SOCKET; MICRO-SD-SOCKET
JP3: PINHD-2X2REVERSED; 2X02/EDGE_REVERSED
L1: 1uH; INDC2009X120
LEFT: SWITCH_MOMENTARYCONTACTIVE_6MM_2; BUTTON-CONDUCTIVE_6MM_2
MOTOR: 61300211121
PMOD1, PMOD2: PINHD-2X6REVERSED; 2X06/EDGE_REVERSED
R1, R2, R3, R4, R5, R6, R7, R8, R9, R10, R11, R20, R21, R22, R23, R24, R25, R26: 10k; RESC1608X60
R12, R13, R27: 5.1k; RESC1608X60
R14: 732k; RESC1608X60
R15: 100k; RESC1608X60
R17, R18: 1k; RESC1608X60
R19: 2.0k; RESC1608X60
REGULATOR: TPS61070; SOT563
RIGHT: SWITCH_MOMENTARYCONTACTIVE_6MM_2; BUTTON-CONDUCTIVE_6MM_2
S1, S2: TL3340AF160QG; TL3340
SELECT: SWITCH_MOMENTARYDMG-BTN-START/SELECT; DMG_BTN1_W2
START: SWITCH_MOMENTARYDMG-BTN-START/SELECT; DMG_BTN1_W2
U1: MAX17048G+T1021-0168E_T822-3_MXM; 21-0168E_T822-3_MXM
U$1: SILKSCREENGBC_D-PAD; GAMEBOY_COLOR_DPAD_SILK
U$2: SILKSCREENGBC_START/SELECT; GAMEBOY_COLOR_START_SELECT_SILK
U$3, U$4: SILKSCREENGBC_A/B; GAMEBOY_COLOR_A/B_BUTTON_MEMBRANE
UP: SWITCH_MOMENTARYCONTACTIVE_6MM_2; BUTTON-CONDUCTIVE_6MM_2
USB-C: 629722000214; USB4110GFA
X: SWITCH_MOMENTARYDMG-BTN-A/B; DMG_BTN3
Y: SWITCH_MOMENTARYDMG-BTN-A/B; DMG_BTN3

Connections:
3V3: C1.1, C3.1, HAPTIC.6, HAPTIC.10, IC1.21, J2.VCC, PMOD1.11, PMOD1.12, PMOD2.11, PMOD2.12, R1.2, R2.2, R3.2, R4.2, R5.2, R6.2, R7.2, R8.2, R9.2, R10.2, R11.2, R17.2, R18.2, R20.2, R21.1, R24.2, R25.2, R26.2
5V: C4.1, C6.1, D1.1, JP3.1, JP3.4, R14.2, REGULATOR.6
!BAT_ALERT: IC1.4, R21.2, U1.5
A: A.P$1, A.P$3, IC1.10, R3.1
B: B.P$1, B.P$3, IC1.11, R4.1
CLK: J2.SCLK, PMOD2.7
CS: J2.CS, PMOD2.1
DOWN: DOWN.1, IC1.6, R8.1
GND: A.P$2, A.P$4, B.P$2, B.P$4, BATT.1, C1.2, C2.2, C3.2, C4.2, C5.2, C6.2, C7.1, DOWN.2, HAPTIC.8, IC1.9, IC1.18, IC1.24, IC1.25, IC2.2, J2.GND, J2.GND1, J2.GND3, JP3.2, JP3.3, LEFT.2, PMOD1.9, PMOD1.10, PMOD2.9, PMOD2.10, R12.1, R13.2, R15.2, R19.1, R23.2, REGULATOR.4, RIGHT.2, S1.2, S2.2, SELECT.P$2, SELECT.P$4, START.P$2, START.P$4, U1.1, U1.4, U1.6, U1.9, UP.2, USB-C.A1, USB-C.A12, USB-C.B1, USB-C.B12, USB-C.MP1, USB-C.MP2, USB-C.MP3, USB-C.MP4, X.P$2, X.P$4, Y.P$2, Y.P$4
GPIO_INTN: IC1.22, PMOD1.3, R26.1
LEFT: IC1.7, LEFT.1, R5.1
M+: HAPTIC.7, MOTOR.1
M-: HAPTIC.9, MOTOR.2
unnamed: R12.2, USB-C.B5
unnamed: R13.1, USB-C.A5
unnamed: R14.1, R15.1, REGULATOR.1
unnamed: L1.2, REGULATOR.5
unnamed: IC2.5, R19.2
unnamed: HAPTIC.5, R20.1
unnamed: IC1.23, R11.1
unnamed: D2.A, R27.2
RIGHT: IC1.8, R6.1, RIGHT.1
SCK: HAPTIC.2, IC1.19, PMOD1.6, R17.1, U1.7
SDA: HAPTIC.3, IC1.20, PMOD1.8, R18.1, U1.8
SELECT: IC1.2, R9.1, SELECT.P$1, SELECT.P$3
SI: J2.DI, PMOD2.3
SO: J2.DO, PMOD2.5
START: IC1.1, R10.1, START.P$1, START.P$3
STAT2: D2.C, IC2.1
UP: IC1.5, R7.1, UP.1
USB_D+: PMOD1.7, USB-C.A6, USB-C.B6
USB_D-: PMOD1.5, USB-C.A7, USB-C.B7
VBAT: BATT.2, C5.1, C7.2, IC2.3, L1.1, R22.1, REGULATOR.2, REGULATOR.3, U1.2, U1.3
VBAT_SENSE: PMOD2.8, R22.2, R23.1
VBUS: C2.1, D1.2, IC2.4, R27.1, USB-C.A4, USB-C.A9, USB-C.B4, USB-C.B9
VOLUME_DOWN: IC1.15, R25.1, S2.1, S2.3
VOLUME_UP: IC1.14, R24.1, S1.1, S1.3
X: IC1.12, R1.1, X.P$1, X.P$3
Y: IC1.13, R2.1, Y.P$1, Y.P$3

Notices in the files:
README.md:
This project is licensed under the terms in [LICENSE](./LICENSE).
parts and their libraries:
SparkFun-IC-Special-Function: Licensing: Creative Commons ShareAlike 4.0 International - https://creativecommons.org/licenses/by-sa/4.0
Wurth_Connectors_WR-USB: Copyright: Würth Elektronik
COPYRIGHT: Copyright (C) 2023 Ultra Librarian. All rights reserved.
